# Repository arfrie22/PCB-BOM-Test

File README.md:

# Proton
1-key keyswitch tester

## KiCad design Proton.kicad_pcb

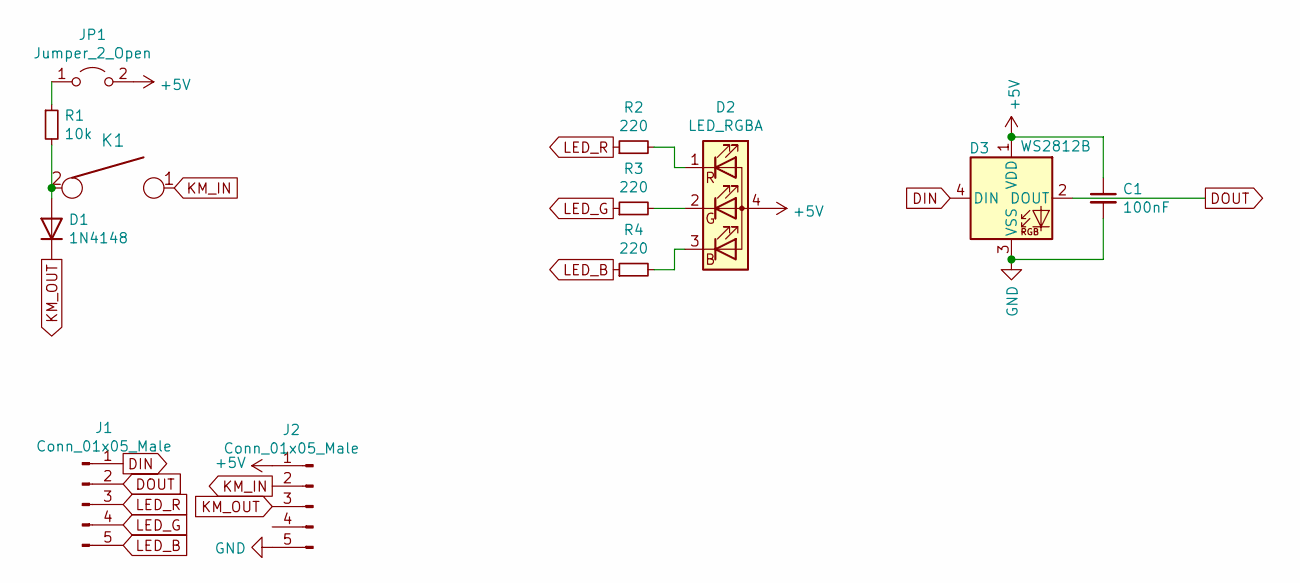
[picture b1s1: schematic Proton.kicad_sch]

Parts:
C1: 100nF; C_0603_1608Metric_Pad1.05x0.95mm_HandSolder
D1: 1N4148; D_SOD-123F
D2: LED_RGBA
D3: WS2812B; LED_WS2812B_PLCC4_5.0x5.0mm_P3.2mm
J1, J2: Conn_01x05_Male; PinHeader_1x05_P2.54mm_Vertical
JP1: Jumper_2_Open; SolderJumper-2_P1.3mm_Open_TrianglePad1.0x1.5mm
K1: KEYSW; Kailh_socket_MX_1u
R1: 10k; R_0603_1608Metric_Pad1.05x0.95mm_HandSolder
R2, R3, R4: 220; R_0603_1608Metric_Pad1.05x0.95mm_HandSolder

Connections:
+5V: C1.1, D2.4 (A), D3.1 (VDD), J2.1, JP1.2 (B)
DIN: D3.4 (DIN), J1.1
DOUT: D3.2 (DOUT), J1.2
GND: C1.2, D3.3 (VSS), J2.5
KM_IN: J2.2, K1.1
KM_OUT: D1.1 (K), J2.3
LED_B: J1.5, R4.1
LED_G: J1.4, R3.1
LED_R: J1.3, R2.1
unnamed: D1.2 (A), K1.2, R1.2
unnamed: D2.1 (RK), R2.2
unnamed: D2.2 (GK), R3.2
unnamed: D2.3 (BK), R4.2
unnamed: JP1.1 (A), R1.1

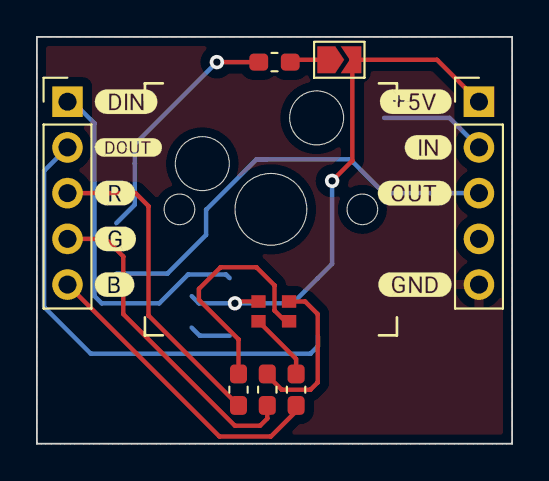
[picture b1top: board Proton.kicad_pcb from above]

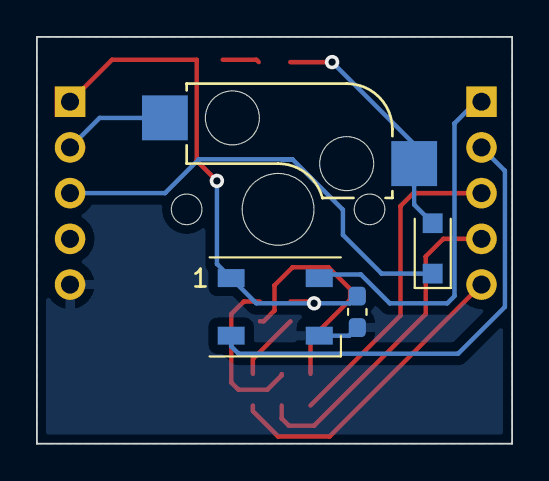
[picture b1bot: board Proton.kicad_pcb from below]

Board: 2 copper layers, 26.4 x 22.6 mm, 12 parts (3 on the bottom side), 14 nets.

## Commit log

2021-10-03 Test
2021-10-03 Create run
2021-11-16 New CI
